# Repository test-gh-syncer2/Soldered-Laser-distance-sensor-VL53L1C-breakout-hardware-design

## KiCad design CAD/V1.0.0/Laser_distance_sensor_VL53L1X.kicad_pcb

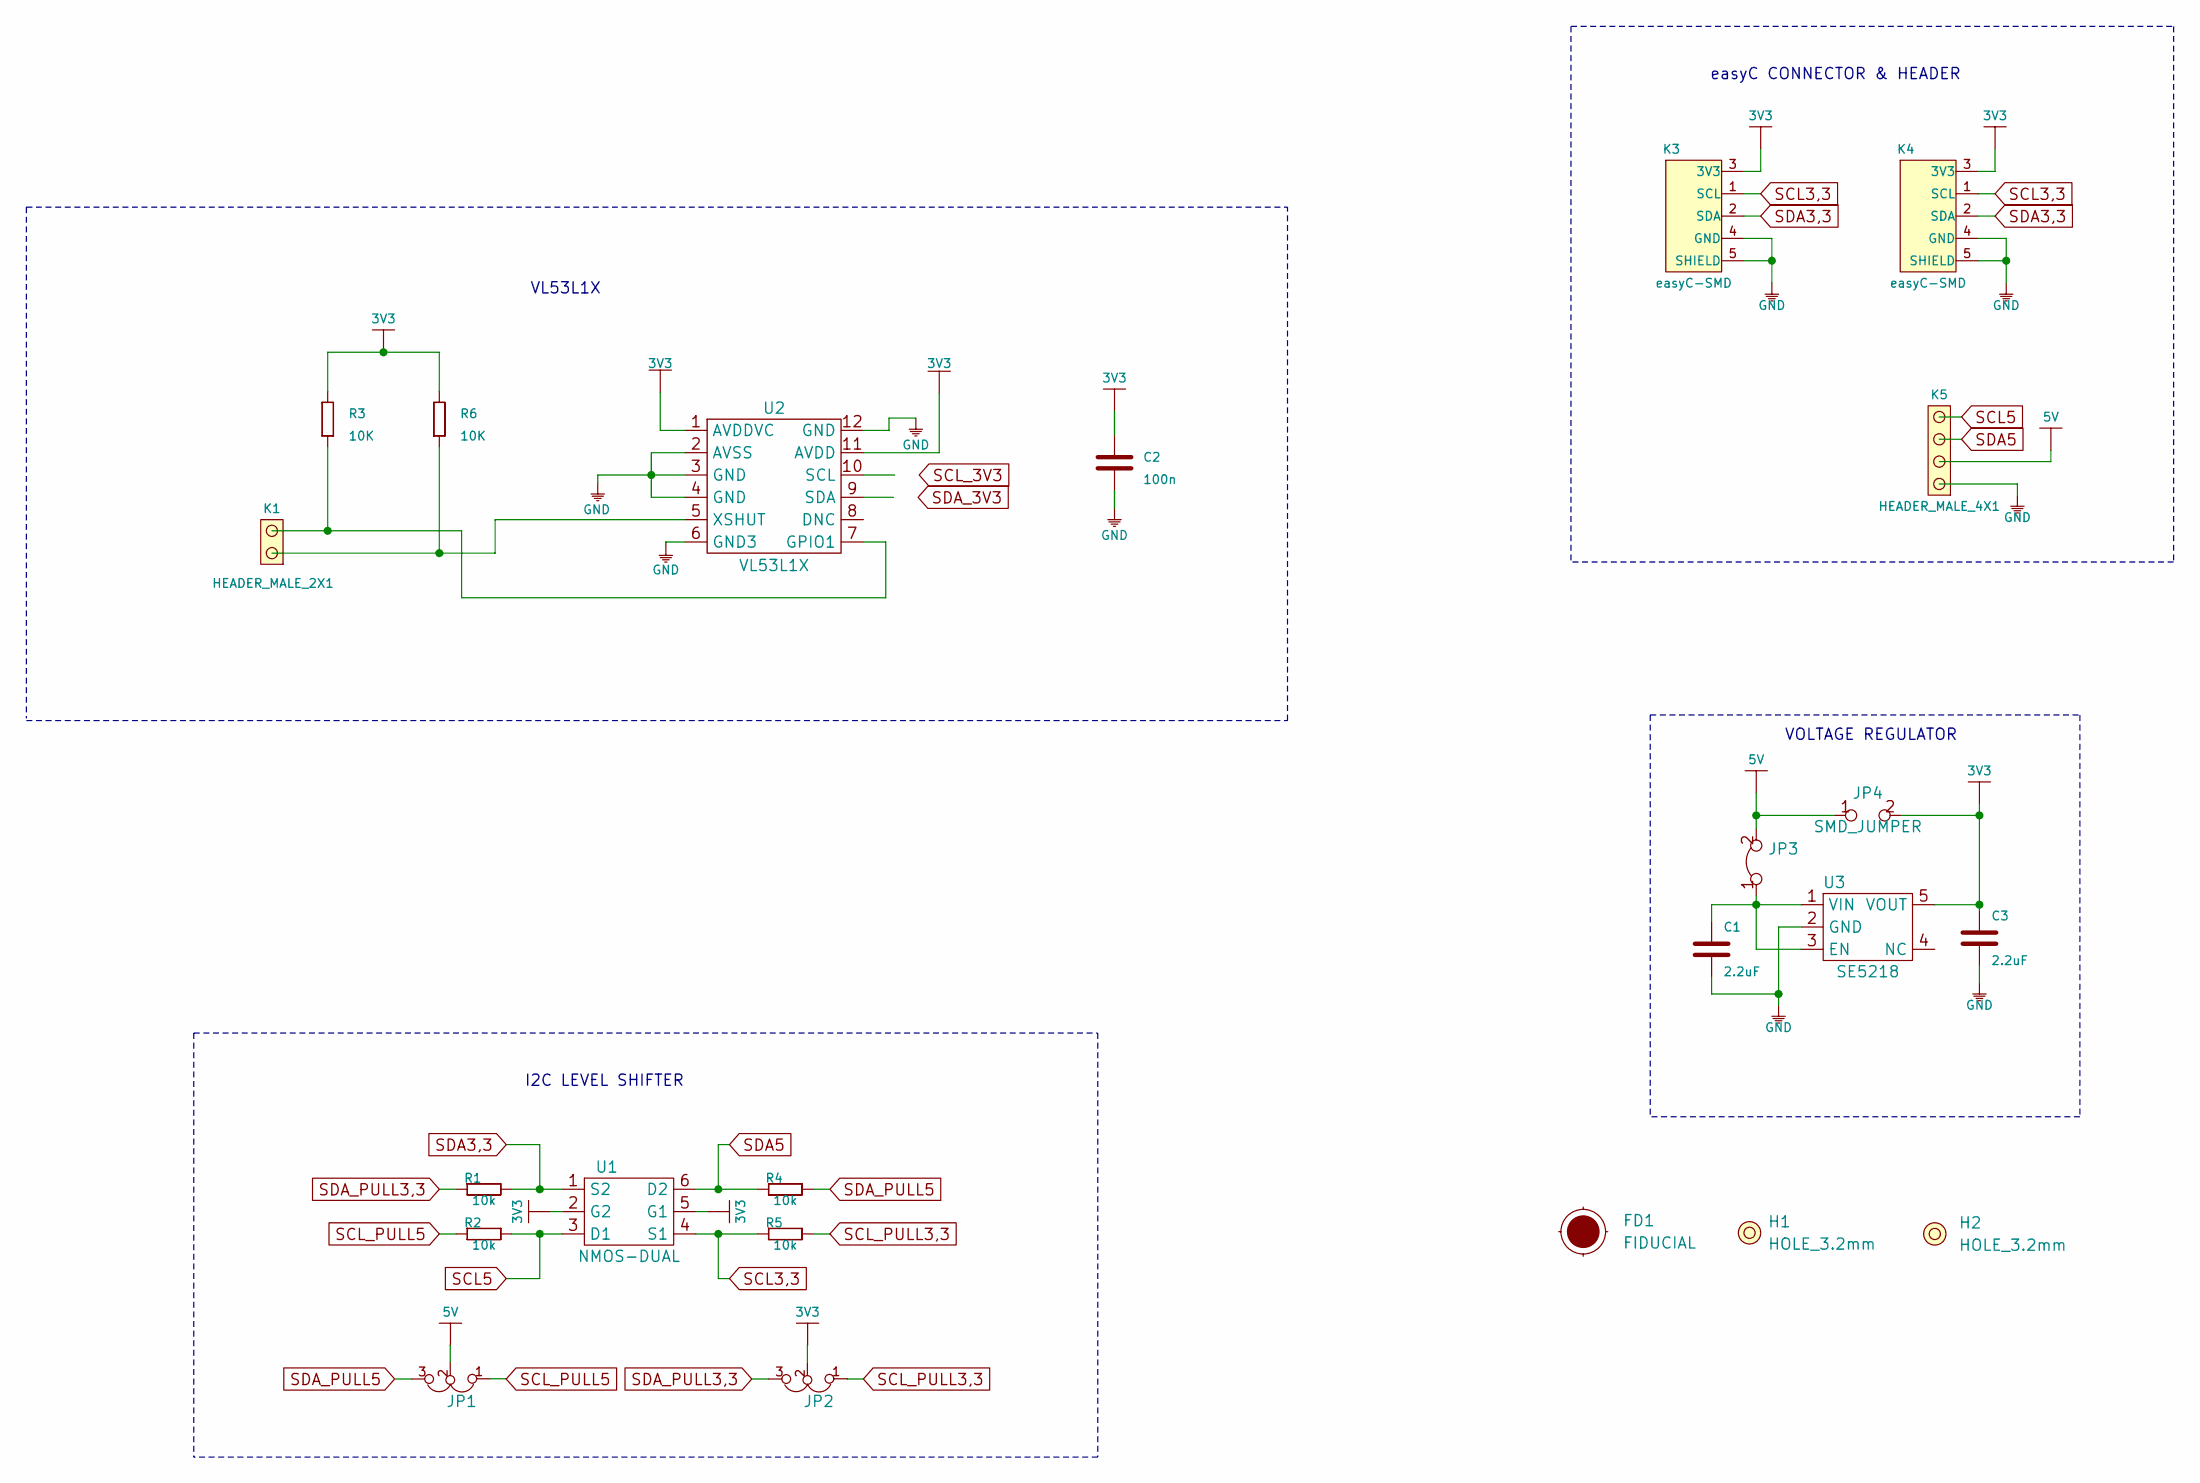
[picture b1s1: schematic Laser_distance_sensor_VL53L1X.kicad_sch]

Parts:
C1, C3: 2.2uF; 0603C
C2: 100n; 0603C
FD1: FIDUCIAL; FIDUCIAL_23
H1, H2: HOLE_3.2mm
JP1, JP2: SMD_JUMPER_3_PAD_TRACE
JP3: SMD-JUMPER-CONNECTED_TRACE_SLODERMASK
JP4: SMD_JUMPER
K1: HEADER_MALE_2X1
K3, K4: easyC-SMD; easyC-connector
K5: HEADER_MALE_4X1
R1, R2, R4, R5: 10k; 0603R
R3, R6: 10K; 0603R
U1: NMOS-DUAL; SOT-363
U2: VL53L1X
U3: SE5218; SOT-23-5

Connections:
3V3: C2.1, C3.2, JP2.2, JP4.2, K3.3 (3V3), K4.3 (3V3), R3.2, R6.2, U1.2 (G2), U1.5 (G1), U2.1 (AVDDVC), U2.11 (AVDD), U3.5 (VOUT)
5V: JP1.2, JP3.2, JP4.1, K5.2
GND: C1.1, C2.2, C3.1, K3.4 (GND), K3.5 (SHIELD), K4.4 (GND), K4.5 (SHIELD), K5.1, U2.2 (AVSS), U2.3 (GND), U2.4 (GND), U2.6 (GND3), U2.12 (GND), U3.2 (GND)
unnamed: C1.2, JP3.1, U3.1 (VIN), U3.3 (EN)
unnamed: K1.1, R6.1, U2.5 (XSHUT)
unnamed: K1.2, R3.1, U2.7 (GPIO1)
SCL3,3: K3.1 (SCL), K4.1 (SCL), R5.1, U1.4 (S1)
SCL5: K5.4, R2.2, U1.3 (D1)
SCL_PULL3,3: JP2.1, R5.2
SCL_PULL5: JP1.1, R2.1
SDA3,3: K3.2 (SDA), K4.2 (SDA), R1.2, U1.1 (S2)
SDA5: K5.3, R4.1, U1.6 (D2)
SDA_PULL3,3: JP2.3, R1.1
SDA_PULL5: JP1.3, R4.2

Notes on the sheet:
VL53L1X
I2C LEVEL SHIFTER
VOLTAGE REGULATOR
easyC CONNECTOR & HEADER

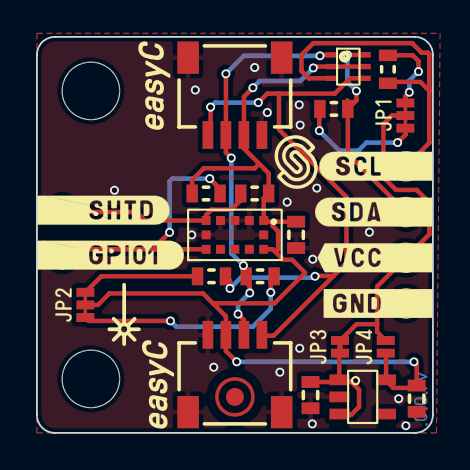
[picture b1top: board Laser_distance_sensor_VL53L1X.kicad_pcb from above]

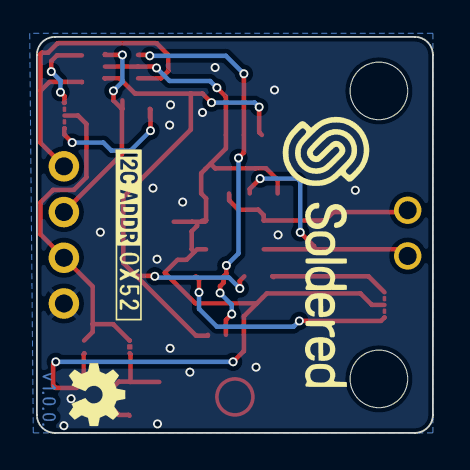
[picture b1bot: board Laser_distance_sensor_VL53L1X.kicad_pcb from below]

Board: 2 copper layers, 22.0 x 22.0 mm, 24 parts (3 on the bottom side), 14 nets.

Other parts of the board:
Ref**: Val**; Version1.0.0.

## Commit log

2021-09-23 Syncing to git
2021-09-23 Updating open source files.
